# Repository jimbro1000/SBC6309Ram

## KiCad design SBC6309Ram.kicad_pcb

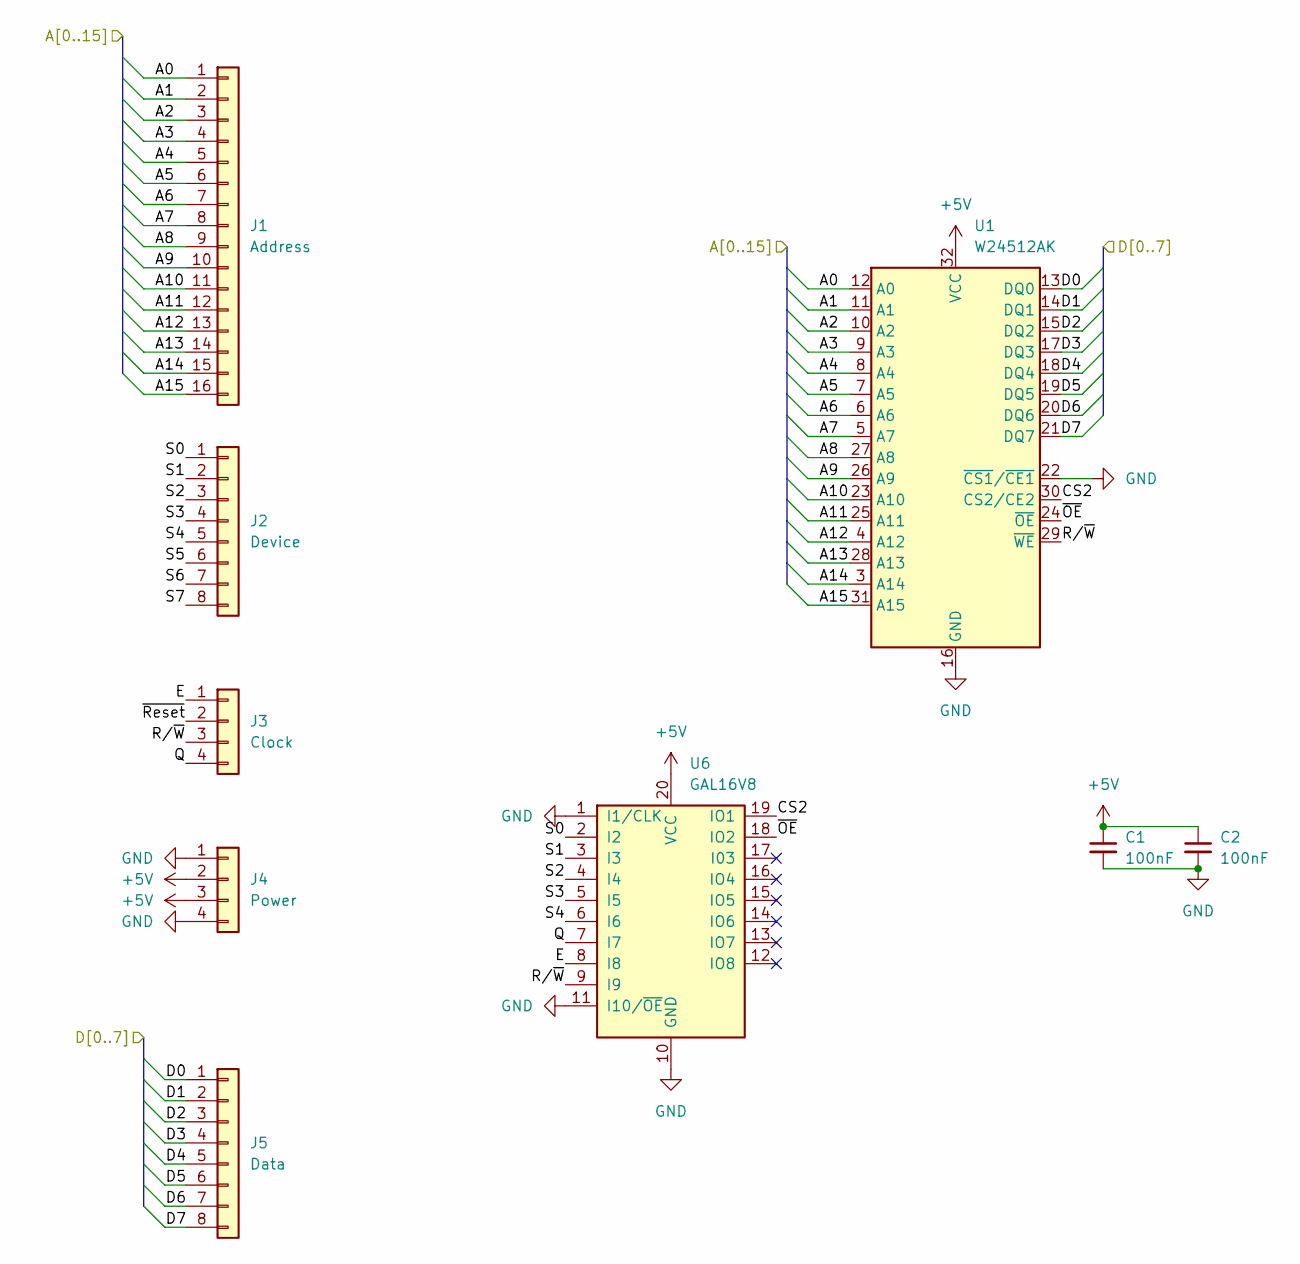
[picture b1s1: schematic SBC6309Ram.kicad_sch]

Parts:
C1, C2: 100nF; C_0805_2012Metric
J1: Address; PinHeader_1x16_P2.54mm_Vertical
J2: Device; PinHeader_1x08_P2.54mm_Vertical
J3: Clock; PinHeader_1x04_P2.54mm_Vertical
J4: Power; PinHeader_1x04_P2.54mm_Vertical
J5: Data; PinHeader_1x08_P2.54mm_Vertical
U1: W24512AK; DIP-32_W7.62mm
U6: GAL16V8; PLCC-20_THT-Socket

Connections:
+5V: C1.1, C2.1, J4.2, J4.3, U1.32 (VCC), U6.20 (VCC)
/A0: J1.1, U1.12 (A0)
/A1: J1.2, U1.11 (A1)
/A2: J1.3, U1.10 (A2)
/A3: J1.4, U1.9 (A3)
/A4: J1.5, U1.8 (A4)
/A5: J1.6, U1.7 (A5)
/A6: J1.7, U1.6 (A6)
/A7: J1.8, U1.5 (A7)
/A8: J1.9, U1.27 (A8)
/A9: J1.10, U1.26 (A9)
/A10: J1.11, U1.23 (A10)
/A11: J1.12, U1.25 (A11)
/A12: J1.13, U1.4 (A12)
/A13: J1.14, U1.28 (A13)
/A14: J1.15, U1.3 (A14)
/A15: J1.16, U1.31 (A15)
/CS2: U1.30 (CS2/CE2), U6.19 (IO1)
/D0: J5.1, U1.13 (DQ0)
/D1: J5.2, U1.14 (DQ1)
/D2: J5.3, U1.15 (DQ2)
/D3: J5.4, U1.17 (DQ3)
/D4: J5.5, U1.18 (DQ4)
/D5: J5.6, U1.19 (DQ5)
/D6: J5.7, U1.20 (DQ6)
/D7: J5.8, U1.21 (DQ7)
/E: J3.1, U6.8 (I8)
/Q: J3.4, U6.7 (I7)
/R/~W: J3.3, U1.29 (~WE), U6.9 (I9)
/S0: J2.1, U6.2 (I2)
/S1: J2.2, U6.3 (I3)
/S2: J2.3, U6.4 (I4)
/S3: J2.4, U6.5 (I5)
/S4: J2.5, U6.6 (I6)
/S5: J2.6
/S6: J2.7
/S7: J2.8
/~OE: U1.24 (~OE), U6.18 (IO2)
/~Reset: J3.2
GND: C1.2, C2.2, J4.1, J4.4, U1.16 (GND), U1.22 (~CS1/~CE1), U6.1 (I1/CLK), U6.10 (GND), U6.11 (I10/~OE)

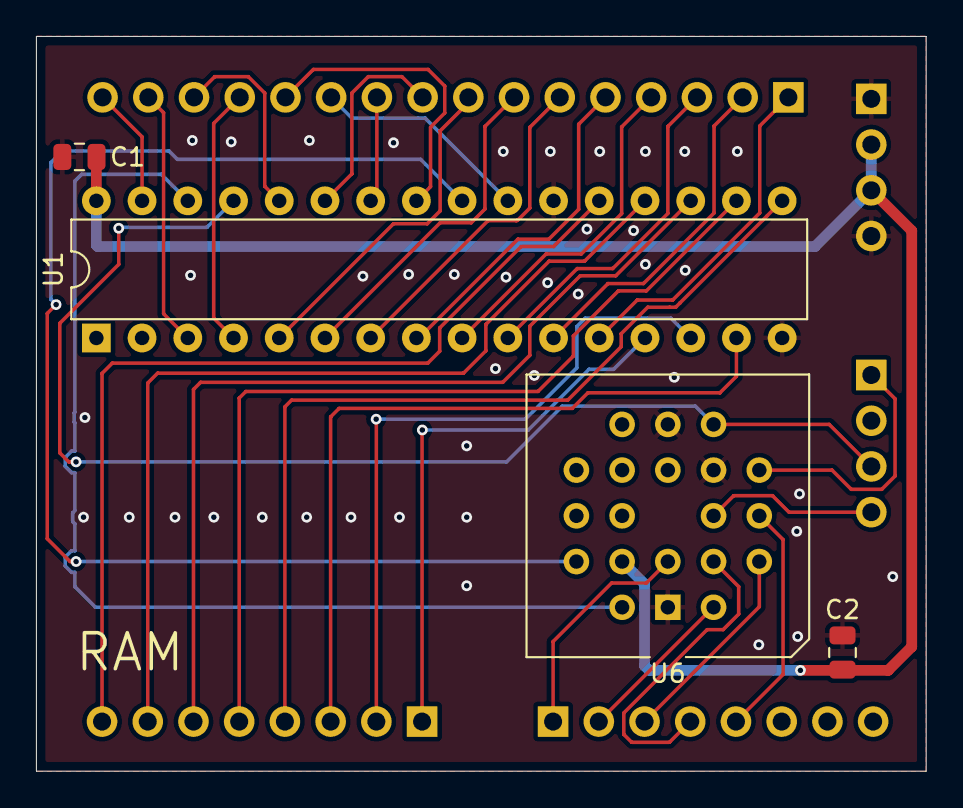
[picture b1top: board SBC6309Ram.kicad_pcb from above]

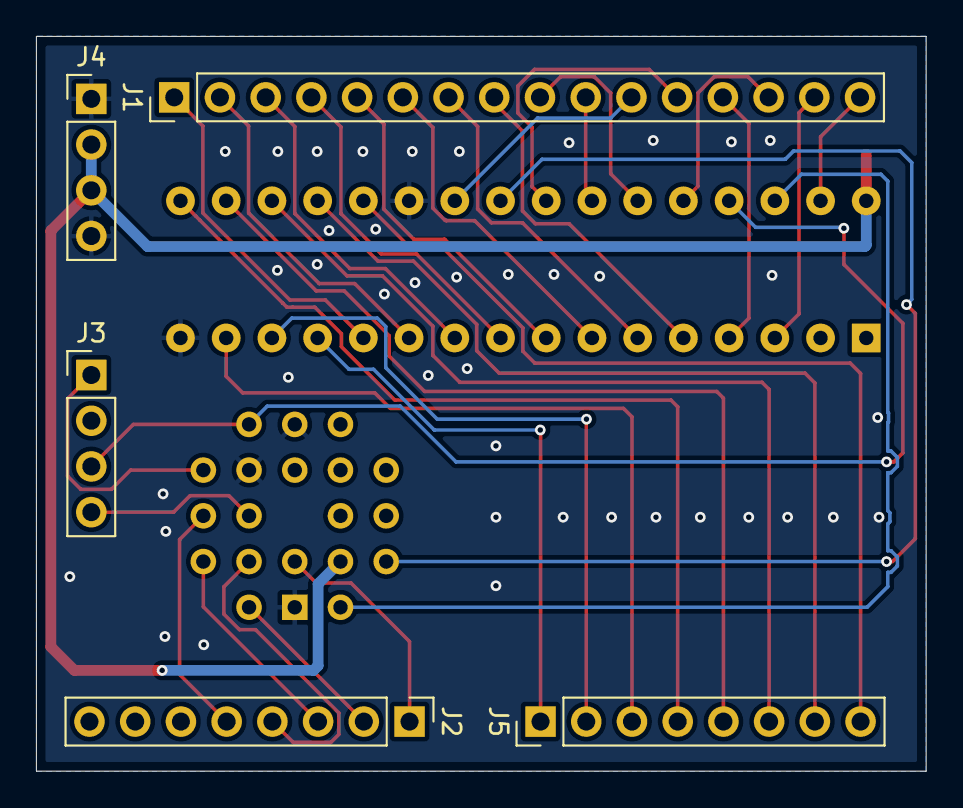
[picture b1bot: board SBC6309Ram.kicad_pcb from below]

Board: 2 copper layers, 49.4 x 40.8 mm, 9 parts (5 on the bottom side), 36 nets.

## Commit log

2025-07-07 minor revision
